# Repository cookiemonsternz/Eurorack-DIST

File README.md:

# DIST

_DIY multi-stage distortion Eurorack module, overdrive, distortion, fuzz, wrmergle, and any combination of them in one handy package_

#### What?
Where VCO was minimal, DIST is maximal! This is a module featuring four different distortion circuits, routed in series with inputs and outputs at every stage in the chain. The four circuits are:
1. Overdrive - Inspired by the Boss SD-1, but with a different tone section and diodes.
2. Distortion - Partly inspired by the RAT, again, many tweaks were made. 
3. Fuzz - Big Muff PI my beloved, slightly different architecture and transistors but still keeping the best tone section in effect I've seen.
4. Wrmergle - A fully custom, from scratch design based on internal feedback, with an adjustable noise gate for your convenience :)

Every circuit has a gain, tone, and volume control, as well as a switch deciding whether to take input from the previous section or from the input jack. The overdrive has a potentiometer instead of a switch, setting an overall feedback control for more fun effects.

#### Why?
Distortion is quite literally the best effect, but no one pedal gives quite enough for me lol. This module has various features which enable absolutely ridiculous gains, while still having some playability due to the noise gate. I also like the idea of having it patchable at any point, as it means you can pick and choose how much distortion (and of what types) you want, or even just use it as 4 seperate distortions in parallel. 

Its definitely a big module, but you do get an absolute crapton of features and control, which is always nice to have.

#### How to use?
The jacks on the left side are the inputs, and on the right the corresponding outputs.
Each section is routed into the next, and you can toggle between using the input jack or the previous stage as input using the switch. The top left knob controls the overall feedback, as in how much of the output of the WRMERGLE stage goes to the input of the OD stage. 

Generally, you should be able to find your way around by following the signal path on the front board.

#### Simulations
I've included the simulations I created on LTSpice; *od.asc*, *dist.asc*, *fuzz.asc*, and *wrmergle.asc* contain their respective distortion stages, *gate.asc* contains the gate circuit of the WRMERGLE section, and *structure.asc* is a pseudo-layout of the whole circuit (not functional).

There is also a livespice simulation of the OVERDRIVE section, but I opted not to further utilise this tool due to lack of cross platform support and performance limitations.

I've also included some audio samples generated through LTSpice in **audio-samples/**, note that these are simulations and are thus not perfect, but they should be reasonably accurate.

## Renders

## Schematics

## Zine Page

## BOM
_Needed is how many I personally need :)_
| Part                             | Quantity | Needed | Source     | Link                                                                                                                                                                 | Lot / Min Amount | Unit    | Net     | Running |
|----------------------------------|----------|--------|------------|----------------------------------------------------------------------------------------------------------------------------------------------------------------------|------------------|---------|---------|---------|
| **Capacitors**                       |          |        |            |                                                                                                                                                                      |                  |         |         |         |
| 1n Cap, 0805                     | 6        | 6      | JLCPCB     | https://jlcpcb.com/partdetail/47657-CL21B102KBCNNNC/C46653                                                                                                           | 1                | $0.0112 | $0.0672 | $0.07   |
| 4.7n Cap, 0805                   | 3        | 3      | JLCPCB     | https://jlcpcb.com/partdetail/2096-0805B472K500NT/C1744                                                                                                              | 1                | $0.0066 | $0.0198 | $0.09   |
| 10n Cap, 0805                    | 2        | 2      | JLCPCB     | https://jlcpcb.com/partdetail/2062-CL21B103KBANNNC/C1710                                                                                                             | 1                | $0.0082 | $0.0164 | $0.10   |
| 22n Cap, 0805                    | 2        | 2      | JLCPCB     | https://jlcpcb.com/partdetail/2081-CL21B223KBANNNC/C1729                                                                                                             | 1                | $0.0097 | $0.0194 | $0.12   |
| 100n Cap, 0805                   | 19       | 19     | JLCPCB     | https://jlcpcb.com/partdetail/YAGEO-CC0805KRX7R9BB104/C49678                                                                                                         | 1                | $0.0066 | $0.1254 | $0.25   |
| 220n Cap, 0805                   | 13       | 13     | JLCPCB     | https://jlcpcb.com/partdetail/5810-CL21B224KBFNNNE/C5378                                                                                                             | 1                | $0.0122 | $0.1586 | $0.41   |
| 1u Cap, 0805                     | 1        | 1      | JLCPCB     | https://jlcpcb.com/partdetail/29074-CL21B105KBFNNNE/C28323                                                                                                           | 1                | $0.0165 | $0.0165 | $0.42   |
| 1u Electrolytic Cap, P1.5xD4.0   | 4        | 0      | LCSC       | https://www.lcsc.com/product-detail/C216323.html?spm=wm.fly.bg.2.xh___wm.sy.dhl.mly.12-0-1&lcsc_vid=QgdcVwJXRQJWBFFSFgMKBQVWEgAMVVEFTgQNA1ZXFlkxVlNeR1JeV1RVRlFaVTtW | 50               | $0.0185 | $0.0000 | $0.42   |
| 2.2u Electrolytic Cap, P1.5xD4.0 | 1        | 0      | LCSC       | https://www.lcsc.com/product-detail/C43343.html                                                                                                                      | 50               | $0.0151 | $0.0000 | $0.42   |
| 4.7u Electrolytic Cap, P1.5xD4.0 | 3        | 0      | LCSC       | https://www.lcsc.com/product-detail/C2873979.html                                                                                                                    | 50               | $0.0114 | $0.0000 | $0.42   |
| 10u Electrolytic Cap, P1.5xD4.0  | 3        | 0      | LCSC       | https://www.lcsc.com/product-detail/C503219.html                                                                                                                     | 50               | $0.0143 | $0.0000 | $0.42   |
| **Resistors**                        |          |        |            |                                                                                                                                                                      |                  |         |         |         |
| 47? Resistor, 0805               | 2        | 2      | JLCPCB     | https://jlcpcb.com/partdetail/18402-0805W8F470JT5E/C17714                                                                                                            | 1                | $0.002  | $0.0030 | $0.43   |
| 150? Resistor, 0805              | 2        | 2      | JLCPCB     | https://jlcpcb.com/partdetail/18159-0805W8F1500T5E/C17471                                                                                                            | 1                | $0.0016 | $0.0032 | $0.43   |
| 560? Resistor, 0805              | 5        | 5      | JLCPCB     | https://jlcpcb.com/partdetail/29388-0805W8F5600T5E/C28636                                                                                                            | 1                | $0.0019 | $0.0095 | $0.44   |
| 1k? Resistor, 0805               | 10       | 10     | JLCPCB     | https://jlcpcb.com/partdetail/18201-0805W8F1001T5E/C17513                                                                                                            | 1                | $0.0021 | $0.0210 | $0.46   |
| 1.5k? Resistor, 0805             | 1        | 1      | JLCPCB     | https://jlcpcb.com/partdetail/4717-0805W8F1501T5E/C4310                                                                                                              | 1                | $0.0015 | $0.0015 | $0.46   |
| 2.2k? Resistor, 0805             | 2        | 2      | JLCPCB     | https://jlcpcb.com/partdetail/18208-0805W8F2201T5E/C17520                                                                                                            | 1                | $0.0015 | $0.0030 | $0.46   |
| 4.7k? Resistor, 0805             | 1        | 1      | JLCPCB     | https://jlcpcb.com/partdetail/18361-0805W8F4701T5E/C17673                                                                                                            | 1                | $0.0016 | $0.0016 | $0.47   |
| 6.8k? Resistor, 0805             | 1        | 1      | JLCPCB     | https://jlcpcb.com/partdetail/18460-0805W8F6801T5E/C17772                                                                                                            | 1                | $0.0017 | $0.0017 | $0.47   |
| 10k? Resistor, 0805              | 10       | 10     | JLCPCB     | https://jlcpcb.com/partdetail/18102-0805W8F1002T5E/C17414                                                                                                            | 1                | $0.0020 | $0.0200 | $0.49   |
| 22k? Resistor, 0805              | 2        | 2      | JLCPCB     | https://jlcpcb.com/partdetail/18248-0805W8F2202T5E/C17560                                                                                                            | 1                | $0.0027 | $0.0054 | $0.49   |
| 39k? Resistor, 0805              | 4        | 4      | JLCPCB     | https://jlcpcb.com/partdetail/26569-0805W8F3902T5E/C25826                                                                                                            | 1                | $0.0018 | $0.0072 | $0.50   |
| 100k? Resistor, 0805             | 13       | 13     | JLCPCB     | https://jlcpcb.com/partdetail/160838-0805W8F1003T5E/C149504                                                                                                          | 1                | $0.0020 | $0.0260 | $0.53   |
| 150k? Resistor, 0805             | 1        | 1      | JLCPCB     | https://jlcpcb.com/partdetail/18158-0805W8F1503T5E/C17470                                                                                                            | 1                | $0.0018 | $0.0018 | $0.53   |
| 200k? Resistor, 0805             | 4        | 4      | JLCPCB     | https://jlcpcb.com/partdetail/18227-0805W8F2003T5E/C17539                                                                                                            | 1                | $0.0021 | $0.0084 | $0.54   |
| 220k? Resistor, 0805             | 2        | 2      | JLCPCB     | https://jlcpcb.com/partdetail/18244-0805W8F2203T5E/C17556                                                                                                            | 1                | $0.0017 | $0.0034 | $0.54   |
| 470k? Resistor, 0805             | 3        | 3      | JLCPCB     | https://jlcpcb.com/partdetail/18397-0805W8F4703T5E/C17709                                                                                                            | 1                | $0.0015 | $0.0045 | $0.54   |
| 1M? Resistor, 0805               | 1        | 1      | JLCPCB     | https://jlcpcb.com/partdetail/18202-0805W8F1004T5E/C17514                                                                                                            | 1                | $0.0010 | $0.0010 | $0.55   |
| 2.2M? Resistor, 0805             | 1        | 1      | JLCPCB     | https://jlcpcb.com/partdetail/26856-0805W8F2204T5E/C26113                                                                                                            | 1                | $0.0033 | $0.0033 | $0.55   |
| **Diodes**                           |          |        |            |                                                                                                                                                                      |                  |         |         |         |
| 1N4148WS, SOD-323                | 12       | 12     | JLCPCB     | https://jlcpcb.com/partdetail/2485-1N4148WS/C2128                                                                                                                    | 1                | $0.0092 | $0.1104 | $0.66   |
| **Other Components**                 |          |        |            |                                                                                                                                                                      |                  |         |         |         |
| TL072CDT                         | 7        | 7      | JLCPCB     | https://jlcpcb.com/partdetail/STMicroelectronics-TL072CDT/C6961                                                                                                      | 1                | $0.1570 | $1.0990 | $1.76   |
| 100k? Potentiometer, �RK09K�     | 14       | 14     | Aliexpress | https://www.aliexpress.com/item/1005007278123055.html                                                                                                                | 5                | $0.2080 | $3.1200 | $4.88   |
| SPDT Switch                      | 3        | 3      | Aliexpress | https://www.aliexpress.com/item/1005005370002265.html                                                                                                                | 5                | $0.8520 | $4.2600 | $9.14   |
| PJ301M-12 Audio Jack             | 8        | 8      | Aliexpress | https://www.aliexpress.com/item/1005004864182675.html                                                                                                                | 10               | $0.4440 | $4.4000 | $13.54  |
| 2x08 IDC Connector               | 1        | 0      | LCSC       | https://www.lcsc.com/product-detail/C7430313.html                                                                                                                    | 5                | $0.0993 | $0.0000 | $13.54  |
| 100k? Trimpot, �3362p�           | 1        | 1      | Aliexpress | https://www.aliexpress.com/item/1005010523079544.html                                                                                                                | 10               | $0.4480 | $4.4800 | $18.02  |
| BC547B NPN BJT                   | 4        | 0      | LCSC       | https://www.lcsc.com/product-detail/C713613.html                                                                                                                     | 10               | $0.0495 | $0.0000 | $18.02  |
| BSP89 N-MOSFET                   | 1        | 1      | JLCPCB     | https://jlcpcb.com/partdetail/VBsemiElec-BSP89VB/C20755324                                                                                                           | 1                | $0.5565 | $0.5565 | $18.57  |
| **Other**                            |          |        |            |                                                                                                                                                                      |                  |         |         |         |
| PCB                              | 1        | 1      | JLCPCB     | NA                                                                                                                                                                   | 5                | $1.6600 | $8.3000 | $26.87  |
| Aluminium Plate (100x200x2mm)    | 1        | 1      | Aliexpress | https://www.aliexpress.com/item/1005007160296738.html                                                                                                                | 1                | $6.2300 | $6.2300 | $33.10  |
| Total                            |          |        |            |                                                                                                                                                                      |                  |         |         | $33.10  |

| Totals                          | Money  |
|---------------------------------|--------|
| Aliexpress, Inc. Shipping + Tax | $24.57 |
| JLCPCB, Inc. Shipping + Tax     | $38.84 |
| Total                           | $63.41 |

## CAD Links
Heres the links to the CAD source, Onshape:
[Panel source](https://cad.onshape.com/documents/a7eabe2ba59f8201542a9705/w/4e0a52924acb1733bd85ab30/e/c5b387347f991d36168a8bde?renderMode=0&uiState=6a1f772945aecca6290d22e6)

## Directory Structure
- **audio-samples/** - Generated audio demos of each subcircuit, through ltspice
- **hardware/**
    - **bom/** - BOM Files (CSV and LibreOffice Calc)
    - **cad/** - CAD Files
        - **render/** - Files for rendering (inc. gltf models)
    - **dist/** - KiCad files
        - **lib/** - External libraries
        - **production/** - Production files (Gerber, etc.)
    - **livespice/** - LiveSpice electrical simulations
    - **ltspice/** - LTSpice electrical simulations
- **journals/**
- **zine/** - Zine page

## References
Circuit design influenced by:
[Electric Druid Classic OD](https://electricdruid.net/designing-a-classic-overdrive/)
[Boss SD-1](https://www.hobby-hour.com/electronics/s/sd1-super-overdrive.php)
[RAT](https://www.electrosmash.com/proco-rat)
[Big Muff PI](https://www.bigmuffpage.com/Big_Muff_Pi_versions_schematics_part1.html)
[One Knob Noise Gate](https://effectslayouts.blogspot.com/2016/07/one-knob-noise-gate.html)

#### This project was created for [Hack Club](https://hackclub.com/) - [Fallout](https://fallout.hackclub.com/)

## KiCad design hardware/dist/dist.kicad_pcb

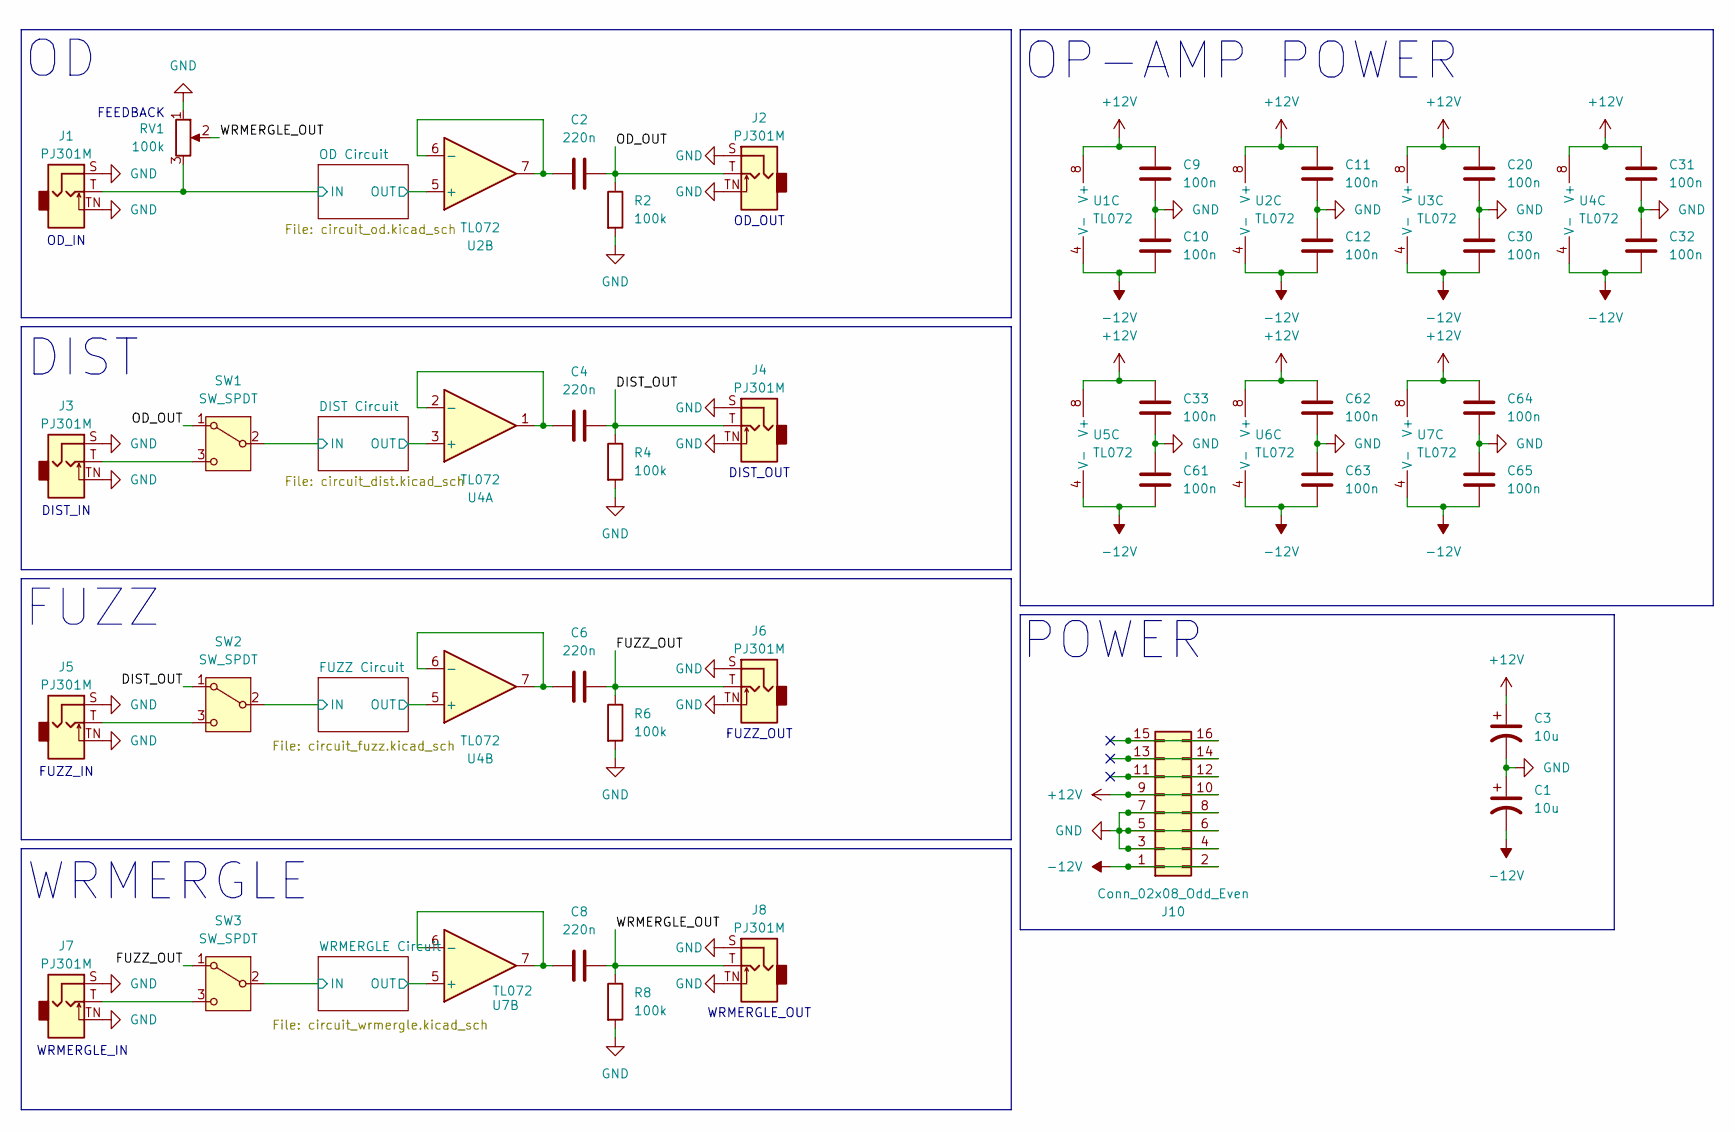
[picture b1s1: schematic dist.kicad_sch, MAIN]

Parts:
C1, C3: 10u; CP_Radial_D4.0mm_P1.50mm
C2, C4, C6, C8: 220n; C_0805_2012Metric_Pad1.18x1.45mm_HandSolder
C9, C10, C11, C12, C20, C30, C31, C32, C33, C61, C62, C63, C64, C65: 100n; C_0805_2012Metric_Pad1.18x1.45mm_HandSolder
J1, J2, J3, J4, J5, J6, J7, J8: PJ301M; Jack_3.5mm_QingPu_WQP-PJ301M-12_Vertical
J10: Conn_02x08_Odd_Even; IDC-Header_2x08_P2.54mm_Vertical
R2, R4, R6, R8: 100k; R_0805_2012Metric_Pad1.20x1.40mm_HandSolder
RV1: 100k; Potentiometer_Alps_RK09K_Single_Vertical
SW1, SW2, SW3: SW_SPDT; PinHeader_1x03_P2.54mm_Vertical
U1, U2, U3, U4, U5, U6, U7: TL072; D8_TEX_STM

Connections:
+12V: C3.1, C9.1, C11.1, C20.1, C31.1, C33.1, C62.1, C64.1, J10.9, J10.10, U1.8 (V+), U2.8 (V+), U3.8 (V+), U4.8 (V+), U5.8 (V+), U6.8 (V+), U7.8 (V+); also elsewhere on the board
-12V: C1.2, C10.2, C12.2, C30.2, C32.2, C61.2, C63.2, C65.2, J10.1, J10.2, U1.4 (V-), U2.4 (V-), U3.4 (V-), U4.4 (V-), U5.4 (V-), U6.4 (V-), U7.4 (V-)
/DIST Circuit/IN: SW1.2 (B); also elsewhere on the board
/DIST Circuit/OUT: U4.3 (+); also elsewhere on the board
/DIST_OUT: C4.2, J4.T, R4.1, SW2.1 (A)
/FUZZ Circuit/IN: SW2.2 (B); also elsewhere on the board
/FUZZ Circuit/OUT: U4.5 (+); also elsewhere on the board
/FUZZ_OUT: C6.2, J6.T, R6.1, SW3.1 (A)
/OD Circuit/IN: J1.T, RV1.3; also elsewhere on the board
/OD Circuit/OUT: U2.5 (+); also elsewhere on the board
/OD_OUT: C2.2, J2.T, R2.1, SW1.1 (A)
/WRMERGLE Circuit/IN: SW3.2 (B); also elsewhere on the board
/WRMERGLE Circuit/OUT: U7.5 (+); also elsewhere on the board
/WRMERGLE_OUT: C8.2, J8.T, R8.1, RV1.2
GND: C1.1, C3.2, C9.2, C10.1, C11.2, C12.1, C20.2, C30.1, C31.2, C32.1, C33.2, C61.1, C62.2, C63.1, C64.2, C65.1, J1.S, J1.TN, J2.S, J2.TN, J3.S, J3.TN, J4.S, J4.TN, J5.S, J5.TN, J6.S, J6.TN, J7.S, J7.TN, J8.S, J8.TN, J10.3, J10.4, J10.5, J10.6, J10.7, J10.8, R2.2, R4.2, R6.2, R8.2, RV1.1; also elsewhere on the board
unnamed: J3.T, SW1.3 (C)
unnamed: J5.T, SW2.3 (C)
unnamed: J7.T, SW3.3 (C)
unnamed: C2.1, U2.6 (-), U2.7
unnamed: C4.1, U4.1, U4.2 (-)
unnamed: C6.1, U4.6 (-), U4.7
unnamed: C8.1, U7.6 (-), U7.7

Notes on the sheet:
DIST_OUT
OD_OUT
FUZZ_OUT
WRMERGLE_OUT
FUZZ
WRMERGLE_IN
FUZZ_IN
DIST_IN
WRMERGLE
OP-AMP POWER
POWER
OD_IN
FEEDBACK
DIST

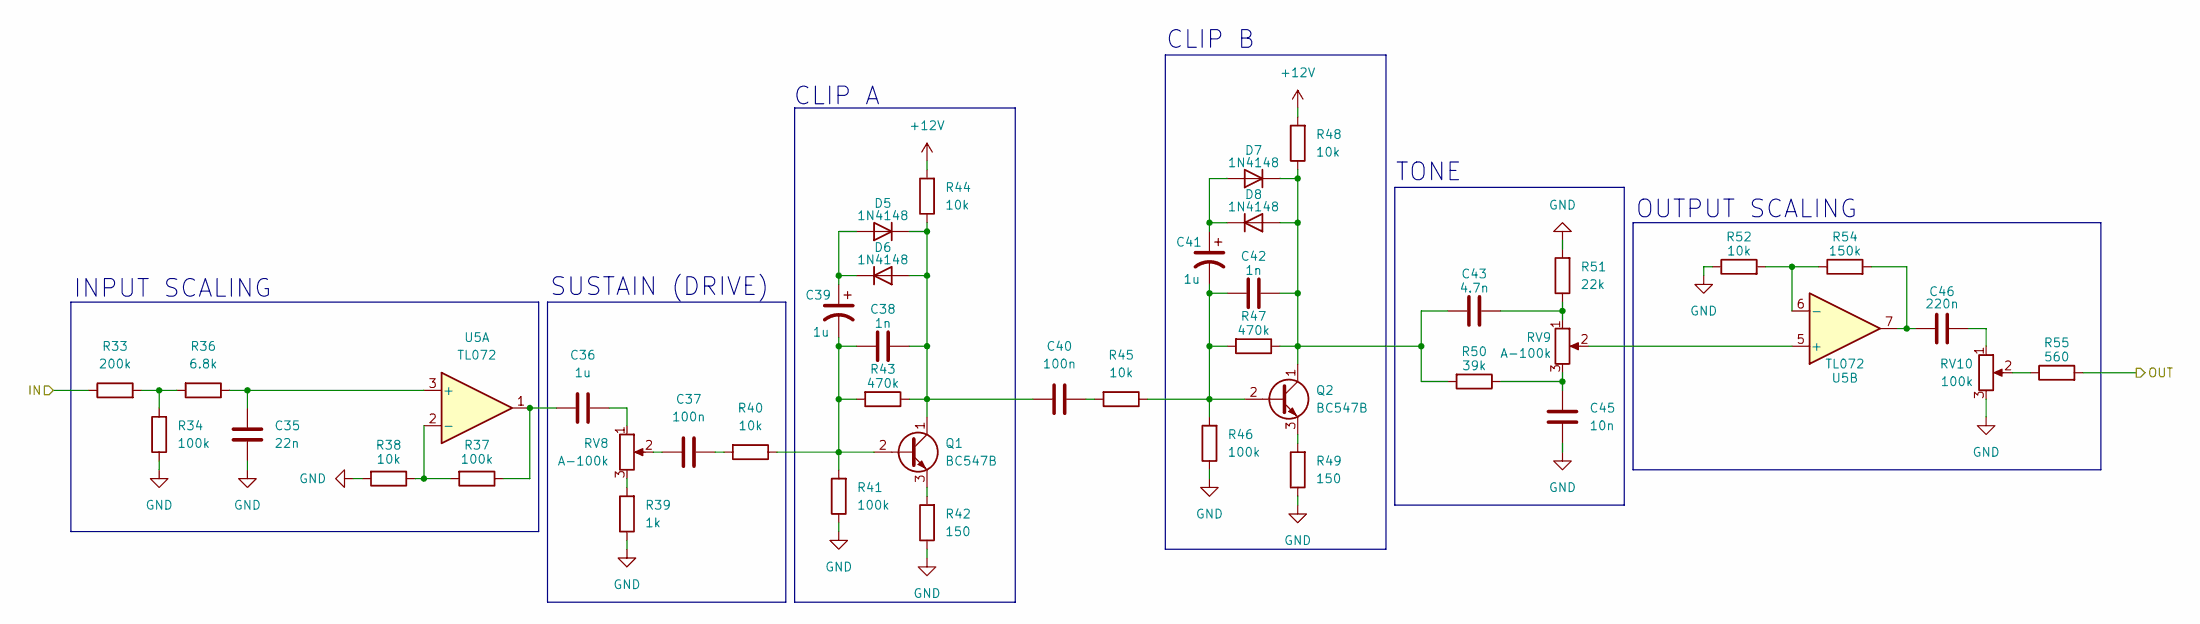
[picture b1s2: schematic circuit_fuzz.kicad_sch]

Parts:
C35: 22n; C_0805_2012Metric_Pad1.18x1.45mm_HandSolder
C36: 1u; C_0805_2012Metric_Pad1.18x1.45mm_HandSolder
C37, C40: 100n; C_0805_2012Metric_Pad1.18x1.45mm_HandSolder
C38, C42: 1n; C_0805_2012Metric_Pad1.18x1.45mm_HandSolder
C39, C41: 1u; CP_Radial_D4.0mm_P1.50mm
C43: 4.7n; C_0805_2012Metric_Pad1.18x1.45mm_HandSolder
C45: 10n; C_0805_2012Metric_Pad1.18x1.45mm_HandSolder
C46: 220n; C_0805_2012Metric_Pad1.18x1.45mm_HandSolder
D5, D6, D7, D8: 1N4148; D_SOD-323
Q1, Q2: BC547B; TO-92_Inline
R33: 200k; R_0805_2012Metric_Pad1.20x1.40mm_HandSolder
R34, R37, R41, R46: 100k; R_0805_2012Metric_Pad1.20x1.40mm_HandSolder
R36: 6.8k; R_0805_2012Metric_Pad1.20x1.40mm_HandSolder
R38, R40, R44, R45, R48, R52: 10k; R_0805_2012Metric_Pad1.20x1.40mm_HandSolder
R39: 1k; R_0805_2012Metric_Pad1.20x1.40mm_HandSolder
R42, R49: 150; R_0805_2012Metric_Pad1.20x1.40mm_HandSolder
R43, R47: 470k; R_0805_2012Metric_Pad1.20x1.40mm_HandSolder
R50: 39k; R_0805_2012Metric_Pad1.20x1.40mm_HandSolder
R51: 22k; R_0805_2012Metric_Pad1.20x1.40mm_HandSolder
R54: 150k; R_0805_2012Metric_Pad1.20x1.40mm_HandSolder
R55: 560; R_0805_2012Metric_Pad1.20x1.40mm_HandSolder
RV8, RV9: A-100k; Potentiometer_Alps_RK09K_Single_Vertical
RV10: 100k; Potentiometer_Alps_RK09K_Single_Vertical
U5: TL072; D8_TEX_STM

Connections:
+12V: R44.2, R48.2; also elsewhere on the board
/FUZZ Circuit/IN: R33.1; also elsewhere on the board
/FUZZ Circuit/OUT: R55.2; also elsewhere on the board
GND: C35.1, C45.1, R34.1, R38.2, R39.1, R41.1, R42.1, R46.1, R49.1, R51.2, R52.1, RV10.3; also elsewhere on the board
unnamed: C36.1, R37.1, U5.1
unnamed: C36.2, RV8.1
unnamed: C37.1, RV8.2
unnamed: C37.2, R40.2
unnamed: C40.2, R45.2
unnamed: C43.2, R51.1, RV9.1
unnamed: C45.2, R50.1, RV9.3
unnamed: C46.1, R54.2, U5.7
unnamed: C46.2, RV10.1
unnamed: C39.1, D5.2 (A), D6.1 (K)
unnamed: C38.2, C40.1, D5.1 (K), D6.2 (A), Q1.1 (C), R43.1, R44.1
unnamed: C41.1, D7.2 (A), D8.1 (K)
unnamed: C42.2, C43.1, D7.1 (K), D8.2 (A), Q2.1 (C), R47.1, R48.1, R50.2
unnamed: C38.1, C39.2, Q1.2 (B), R40.1, R41.2, R43.2
unnamed: Q1.3 (E), R42.2
unnamed: C41.2, C42.1, Q2.2 (B), R45.1, R46.2, R47.2
unnamed: Q2.3 (E), R49.2
unnamed: R33.2, R34.2, R36.2
unnamed: R39.2, RV8.3
unnamed: R55.1, RV10.2
unnamed: C35.2, R36.1, U5.3 (+)
unnamed: R37.2, R38.1, U5.2 (-)
unnamed: RV9.2, U5.5 (+)
unnamed: R52.2, R54.1, U5.6 (-)

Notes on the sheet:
SUSTAIN (DRIVE)
TONE
CLIP B
OUTPUT SCALING
CLIP A
INPUT SCALING

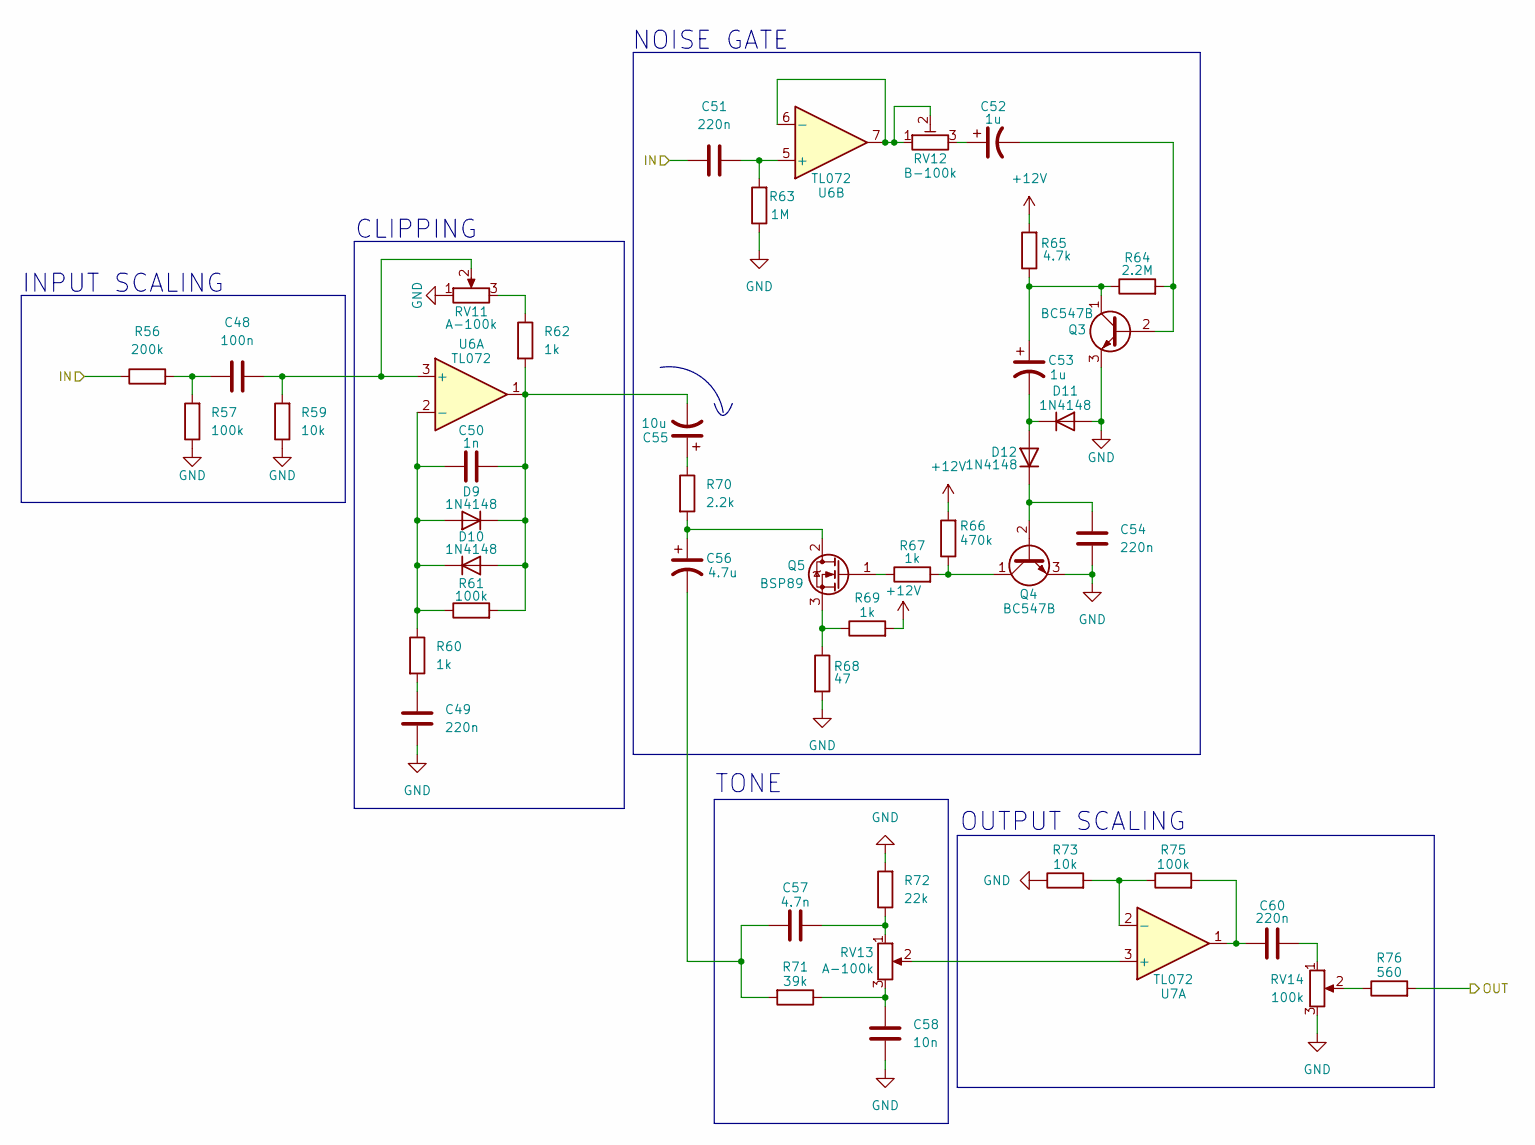
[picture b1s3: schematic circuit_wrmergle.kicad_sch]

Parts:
C48: 100n; C_0805_2012Metric_Pad1.18x1.45mm_HandSolder
C49, C51, C54, C60: 220n; C_0805_2012Metric_Pad1.18x1.45mm_HandSolder
C50: 1n; C_0805_2012Metric_Pad1.18x1.45mm_HandSolder
C52, C53: 1u; CP_Radial_D4.0mm_P1.50mm
C55: 10u; CP_Radial_D4.0mm_P1.50mm
C56: 4.7u; CP_Radial_D4.0mm_P1.50mm
C57: 4.7n; C_0805_2012Metric_Pad1.18x1.45mm_HandSolder
C58: 10n; C_0805_2012Metric_Pad1.18x1.45mm_HandSolder
D9, D10, D11, D12: 1N4148; D_SOD-323
Q3, Q4: BC547B; TO-92_Inline
Q5: BSP89; SOT-223-3_TabPin2
R56: 200k; R_0805_2012Metric_Pad1.20x1.40mm_HandSolder
R57, R61, R75: 100k; R_0805_2012Metric_Pad1.20x1.40mm_HandSolder
R59, R73: 10k; R_0805_2012Metric_Pad1.20x1.40mm_HandSolder
R60, R62, R67, R69: 1k; R_0805_2012Metric_Pad1.20x1.40mm_HandSolder
R63: 1M; R_0805_2012Metric_Pad1.20x1.40mm_HandSolder
R64: 2.2M; R_0805_2012Metric_Pad1.20x1.40mm_HandSolder
R65: 4.7k; R_0805_2012Metric_Pad1.20x1.40mm_HandSolder
R66: 470k; R_0805_2012Metric_Pad1.20x1.40mm_HandSolder
R68: 47; R_0805_2012Metric_Pad1.20x1.40mm_HandSolder
R70: 2.2k; R_0805_2012Metric_Pad1.20x1.40mm_HandSolder
R71: 39k; R_0805_2012Metric_Pad1.20x1.40mm_HandSolder
R72: 22k; R_0805_2012Metric_Pad1.20x1.40mm_HandSolder
R76: 560; R_0805_2012Metric_Pad1.20x1.40mm_HandSolder
RV11, RV13: A-100k; Potentiometer_Alps_RK09K_Single_Vertical
RV12: B-100k; TRIM_3362P-1-253LF
RV14: 100k; Potentiometer_Alps_RK09K_Single_Vertical
U6, U7: TL072; D8_TEX_STM

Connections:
+12V: R65.2, R66.2, R69.2; also elsewhere on the board
/WRMERGLE Circuit/IN: C51.1, R56.1; also elsewhere on the board
/WRMERGLE Circuit/OUT: R76.2; also elsewhere on the board
GND: C49.2, C54.1, C58.1, D11.2 (A), Q3.3 (E), Q4.3 (E), R57.1, R59.1, R63.1, R68.2, R72.2, R73.1, RV11.1, RV14.3; also elsewhere on the board
unnamed: C48.1, R56.2, R57.2
unnamed: C49.1, R60.2
unnamed: C52.1, RV12.3
unnamed: C55.1, R70.1
unnamed: C56.2, C57.1, R71.2
unnamed: C57.2, R72.1, RV13.1
unnamed: C58.2, R71.1, RV13.3
unnamed: C60.1, R75.2, U7.1
unnamed: C60.2, RV14.1
unnamed: C50.2, C55.2, D9.1 (K), D10.2 (A), R61.2, R62.2, U6.1
unnamed: C50.1, D9.2 (A), D10.1 (K), R60.1, R61.1, U6.2 (-)
unnamed: C53.2, D11.1 (K), D12.2 (A)
unnamed: C54.2, D12.1 (K), Q4.2 (B)
unnamed: C52.2, Q3.2 (B), R64.2
unnamed: C53.1, Q3.1 (C), R64.1, R65.1
unnamed: Q4.1 (C), R66.1, R67.2
unnamed: C56.1, Q5.2 (D), R70.2
unnamed: Q5.1 (G), R67.1
unnamed: Q5.3 (S), R68.1, R69.1
unnamed: R62.1, RV11.3
unnamed: R76.1, RV14.2
unnamed: C48.2, R59.2, RV11.2, U6.3 (+)
unnamed: C51.2, R63.2, U6.5 (+)
unnamed: RV12.1, RV12.2, U6.6 (-), U6.7
unnamed: RV13.2, U7.3 (+)
unnamed: R73.2, R75.1, U7.2 (-)

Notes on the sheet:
NOISE GATE
CLIPPING
TONE
INPUT SCALING
OUTPUT SCALING

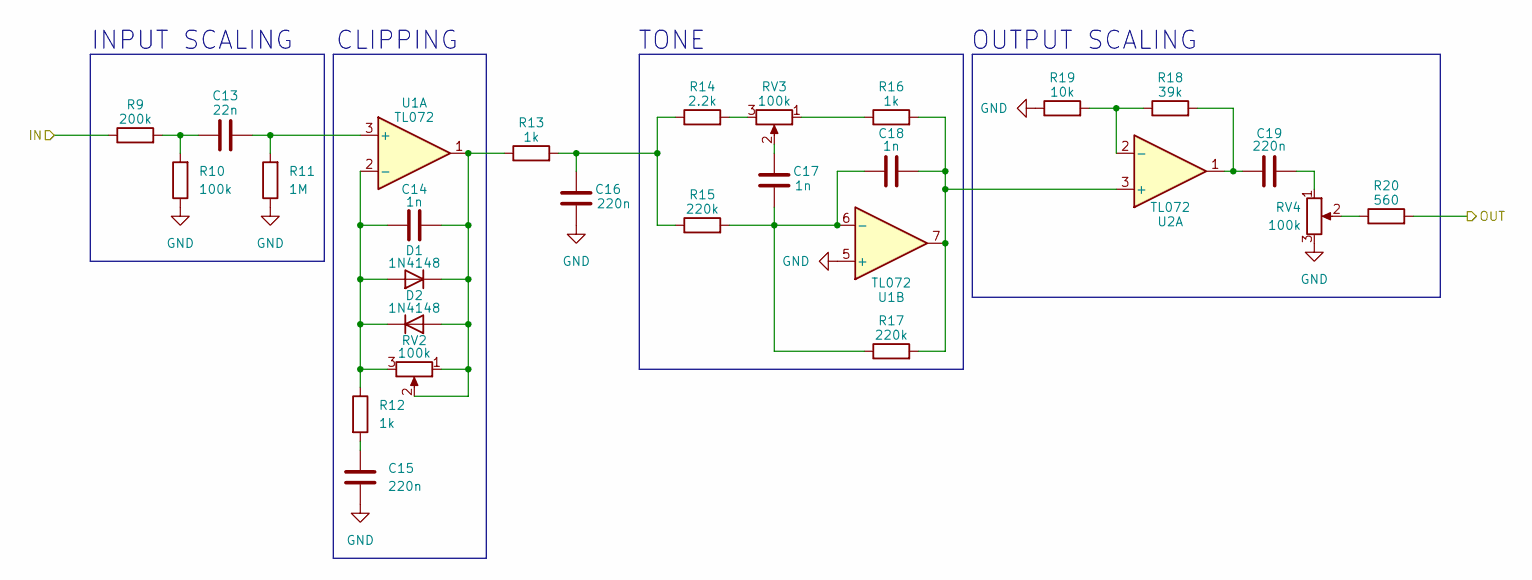
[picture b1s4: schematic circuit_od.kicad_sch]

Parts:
C13: 22n; C_0805_2012Metric_Pad1.18x1.45mm_HandSolder
C14, C17, C18: 1n; C_0805_2012Metric_Pad1.18x1.45mm_HandSolder
C15, C16, C19: 220n; C_0805_2012Metric_Pad1.18x1.45mm_HandSolder
D1, D2: 1N4148; D_SOD-323
R9: 200k; R_0805_2012Metric_Pad1.20x1.40mm_HandSolder
R10: 100k; R_0805_2012Metric_Pad1.20x1.40mm_HandSolder
R11: 1M; R_0805_2012Metric_Pad1.20x1.40mm_HandSolder
R12, R13, R16: 1k; R_0805_2012Metric_Pad1.20x1.40mm_HandSolder
R14: 2.2k; R_0805_2012Metric_Pad1.20x1.40mm_HandSolder
R15, R17: 220k; R_0805_2012Metric_Pad1.20x1.40mm_HandSolder
R18: 39k; R_0805_2012Metric_Pad1.20x1.40mm_HandSolder
R19: 10k; R_0805_2012Metric_Pad1.20x1.40mm_HandSolder
R20: 560; R_0805_2012Metric_Pad1.20x1.40mm_HandSolder
RV2, RV3, RV4: 100k; Potentiometer_Alps_RK09K_Single_Vertical
U1, U2: TL072; D8_TEX_STM

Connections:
/OD Circuit/IN: R9.1; also elsewhere on the board
/OD Circuit/OUT: R20.2; also elsewhere on the board
GND: C15.2, C16.2, R10.1, R11.1, R19.1, RV4.3, U1.5 (+); also elsewhere on the board
unnamed: C13.1, R9.2, R10.2
unnamed: C15.1, R12.2
unnamed: C16.1, R13.2, R14.1, R15.1
unnamed: C17.1, RV3.2
unnamed: C19.1, R18.2, U2.1
unnamed: C19.2, RV4.1
unnamed: C14.1, D1.2 (A), D2.1 (K), R12.1, RV2.3, U1.2 (-)
unnamed: C14.2, D1.1 (K), D2.2 (A), R13.1, RV2.1, RV2.2, U1.1
unnamed: R14.2, RV3.3
unnamed: R16.1, RV3.1
unnamed: R20.1, RV4.2
unnamed: C13.2, R11.2, U1.3 (+)
unnamed: C17.2, C18.1, R15.2, R17.1, U1.6 (-)
unnamed: C18.2, R16.2, R17.2, U1.7, U2.3 (+)
unnamed: R18.1, R19.2, U2.2 (-)

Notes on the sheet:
TONE
CLIPPING
OUTPUT SCALING
INPUT SCALING

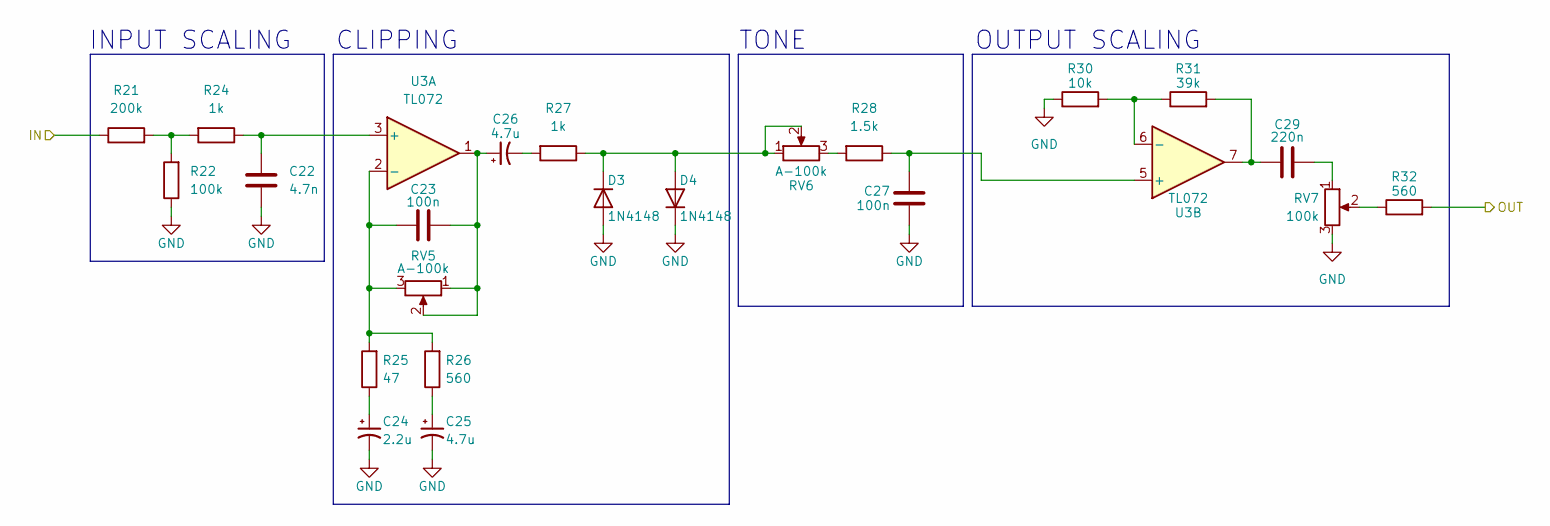
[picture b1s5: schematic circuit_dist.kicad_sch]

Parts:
C22: 4.7n; C_0805_2012Metric_Pad1.18x1.45mm_HandSolder
C23, C27: 100n; C_0805_2012Metric_Pad1.18x1.45mm_HandSolder
C24: 2.2u; CP_Radial_D4.0mm_P1.50mm
C25, C26: 4.7u; CP_Radial_D4.0mm_P1.50mm
C29: 220n; C_0805_2012Metric_Pad1.18x1.45mm_HandSolder
D3, D4: 1N4148; D_SOD-323
R21: 200k; R_0805_2012Metric_Pad1.20x1.40mm_HandSolder
R22: 100k; R_0805_2012Metric_Pad1.20x1.40mm_HandSolder
R24, R27: 1k; R_0805_2012Metric_Pad1.20x1.40mm_HandSolder
R25: 47; R_0805_2012Metric_Pad1.20x1.40mm_HandSolder
R26, R32: 560; R_0805_2012Metric_Pad1.20x1.40mm_HandSolder
R28: 1.5k; R_0805_2012Metric_Pad1.20x1.40mm_HandSolder
R30: 10k; R_0805_2012Metric_Pad1.20x1.40mm_HandSolder
R31: 39k; R_0805_2012Metric_Pad1.20x1.40mm_HandSolder
RV5, RV6: A-100k; Potentiometer_Alps_RK09K_Single_Vertical
RV7: 100k; Potentiometer_Alps_RK09K_Single_Vertical
U3: TL072; D8_TEX_STM

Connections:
/DIST Circuit/IN: R21.1; also elsewhere on the board
/DIST Circuit/OUT: R32.2; also elsewhere on the board
GND: C22.1, C24.2, C25.2, C27.1, D3.2 (A), D4.1 (K), R22.1, R30.1, RV7.3; also elsewhere on the board
unnamed: C23.2, C26.1, RV5.1, RV5.2, U3.1
unnamed: C24.1, R25.1
unnamed: C25.1, R26.1
unnamed: C26.2, R27.2
unnamed: C29.1, R31.2, U3.7
unnamed: C29.2, RV7.1
unnamed: D3.1 (K), D4.2 (A), R27.1, RV6.1, RV6.2
unnamed: R21.2, R22.2, R24.2
unnamed: R28.2, RV6.3
unnamed: R32.1, RV7.2
unnamed: C22.2, R24.1, U3.3 (+)
unnamed: C23.1, R25.2, R26.2, RV5.3, U3.2 (-)
unnamed: C27.2, R28.1, U3.5 (+)
unnamed: R30.2, R31.1, U3.6 (-)

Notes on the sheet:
INPUT SCALING
TONE
OUTPUT SCALING
CLIPPING

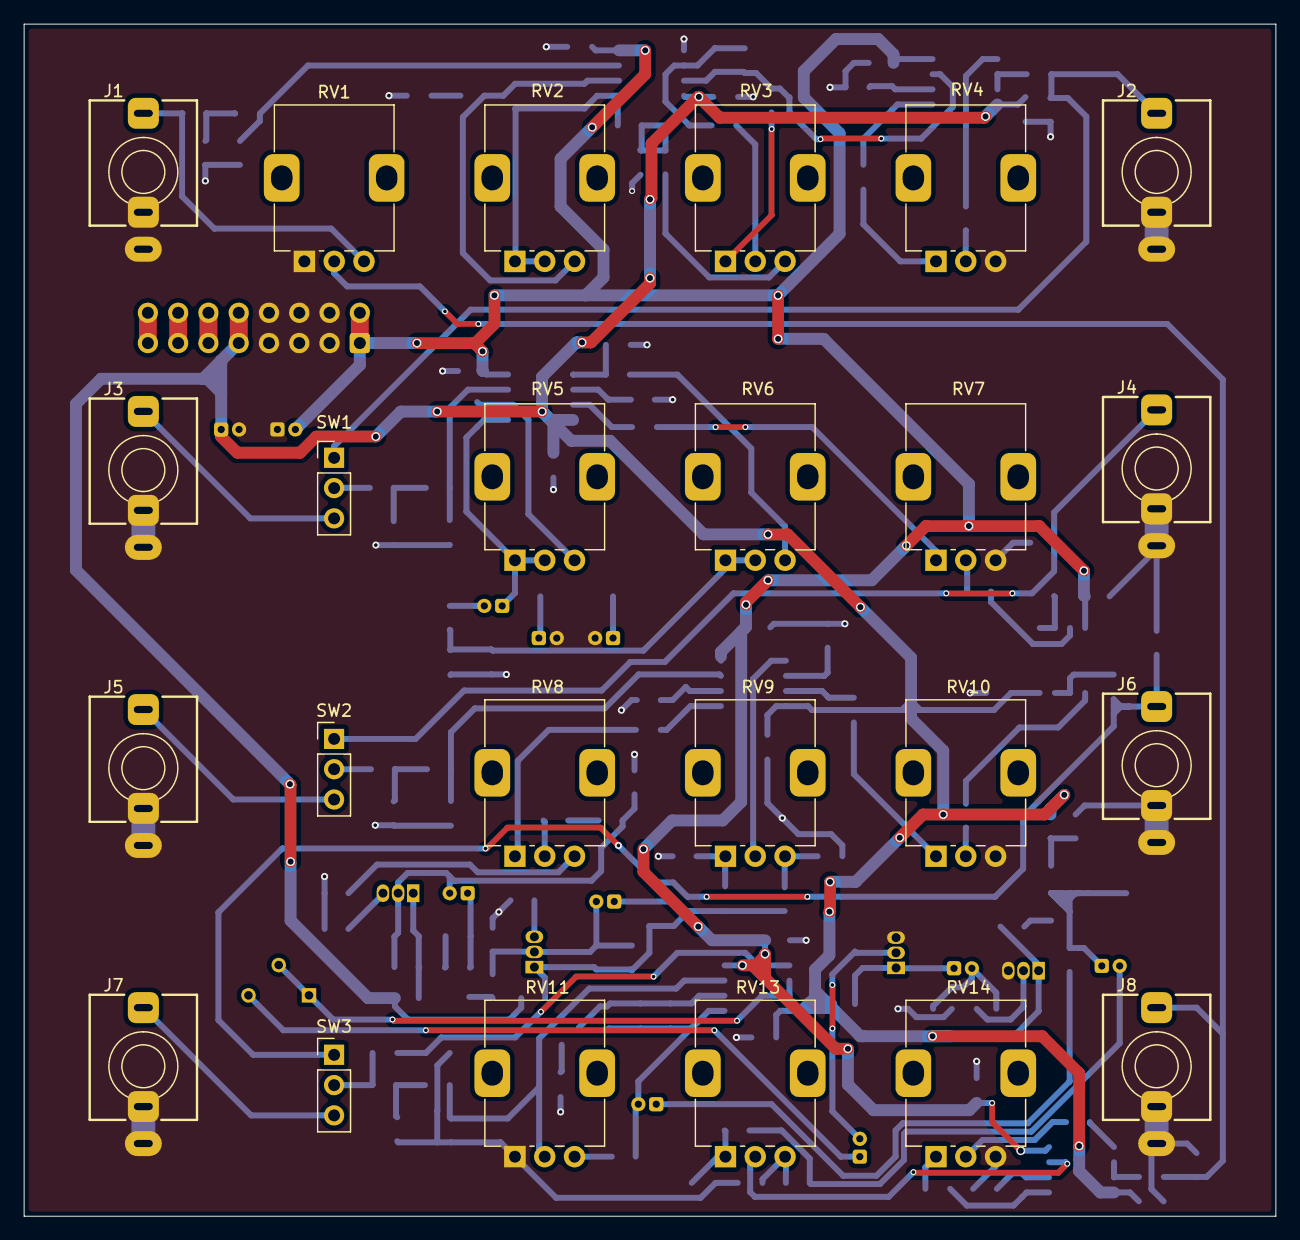
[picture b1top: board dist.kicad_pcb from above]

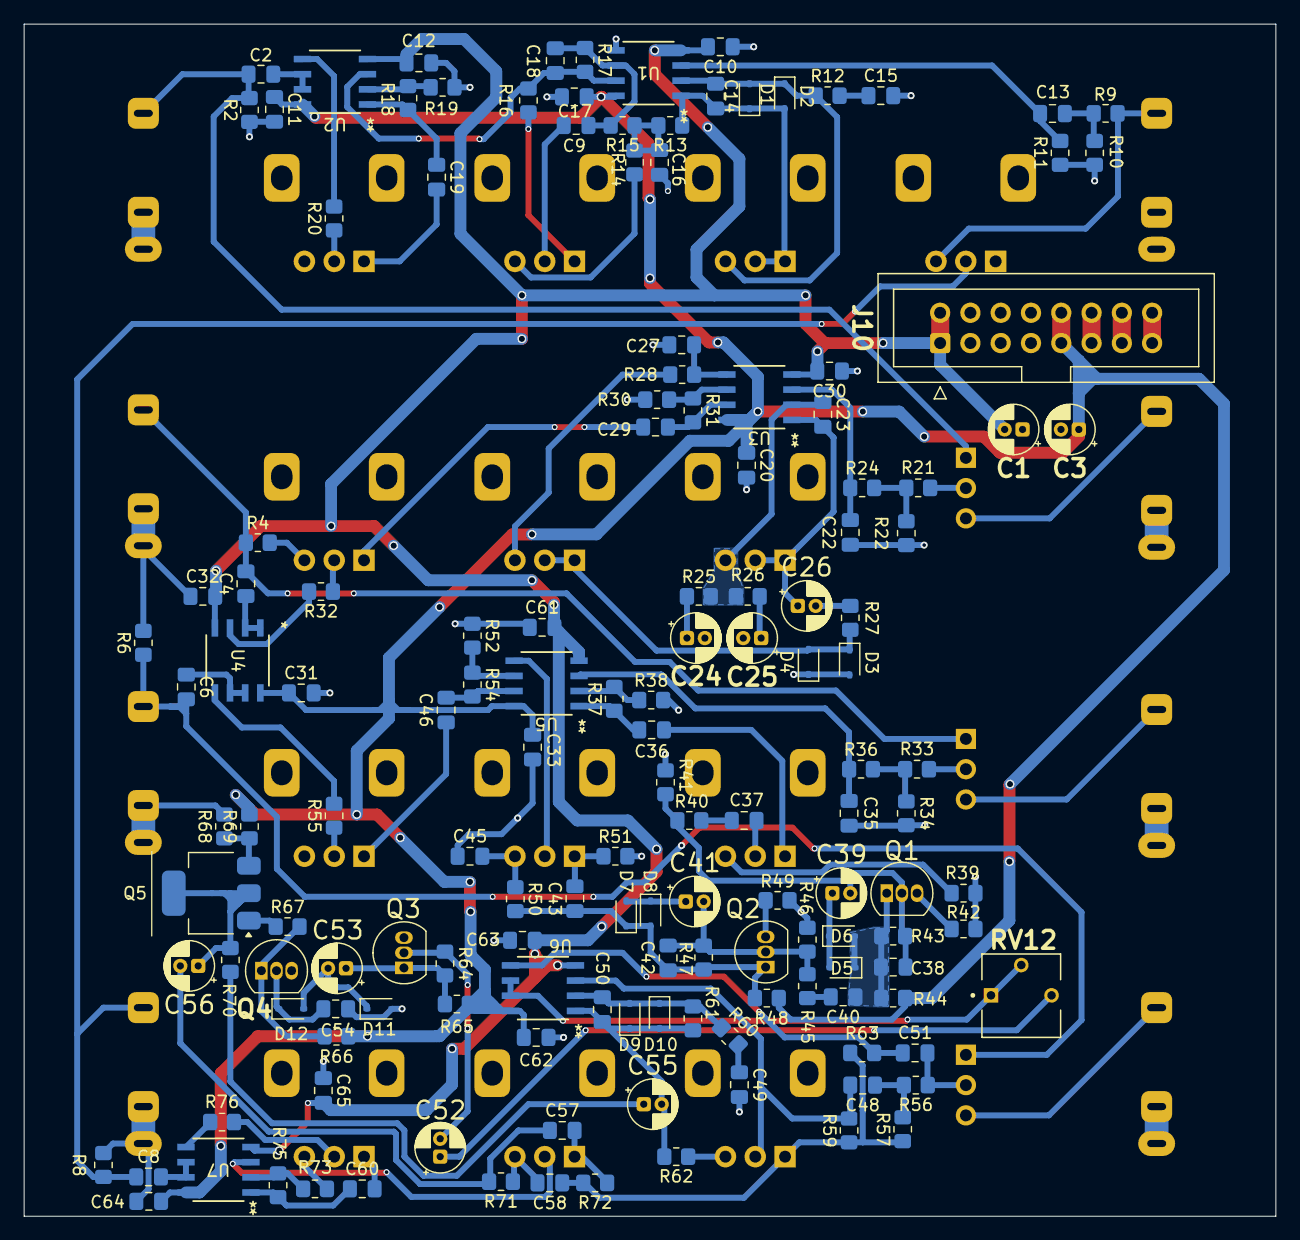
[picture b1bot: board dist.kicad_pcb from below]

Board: 2 copper layers, 105.0 x 100.0 mm, 173 parts (149 on the bottom side), 101 nets.

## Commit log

2026-05-16 stuffs
2026-05-17 update gitignore
2026-05-17 new circuits
    Former-commit-id: 70c6545935585a71ad606ec7b30507693d0ee072
2026-05-17 remove unneeded logs and update gitinore again
    Former-commit-id: 625b2dcab7bd4e79c4723fad000d47b131dc5d98
2026-05-18 new journal
2026-05-31 Start work on combined stuff :)
2026-05-31 Journal
2026-05-31 kicad
2026-06-01 fix for dual supply
2026-06-01 bom + kicad fix for dual supply
2026-06-01 Libreoffice gitignore, bom
2026-06-02 finish pcb
2026-06-03 readme
2026-06-03 Zine
2026-06-03 audio samples
2026-06-03 rm temp
2026-06-03 Finalise readme
2026-06-03 fdinal deets
2026-06-07 add schematics to readme
